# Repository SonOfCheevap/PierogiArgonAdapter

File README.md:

# Pierogi Argon Adapter
These are EAGLE files, may or may not work in KiCad

Created by the head engineer of Big PP Industries

Used to help you better interface with a Particle Argon. Newest version includes a mosfet on the SD Card Reader, and USB C.

Feature List:

-SD Card Reader

-MOSFET to reset the SD Card Reader

-USB C (Power Only)

-2 Relays

-32 Pin header for easy access to each pin

# The Family so Far:

V1(.01)

V1.1

V1.2

V1.3

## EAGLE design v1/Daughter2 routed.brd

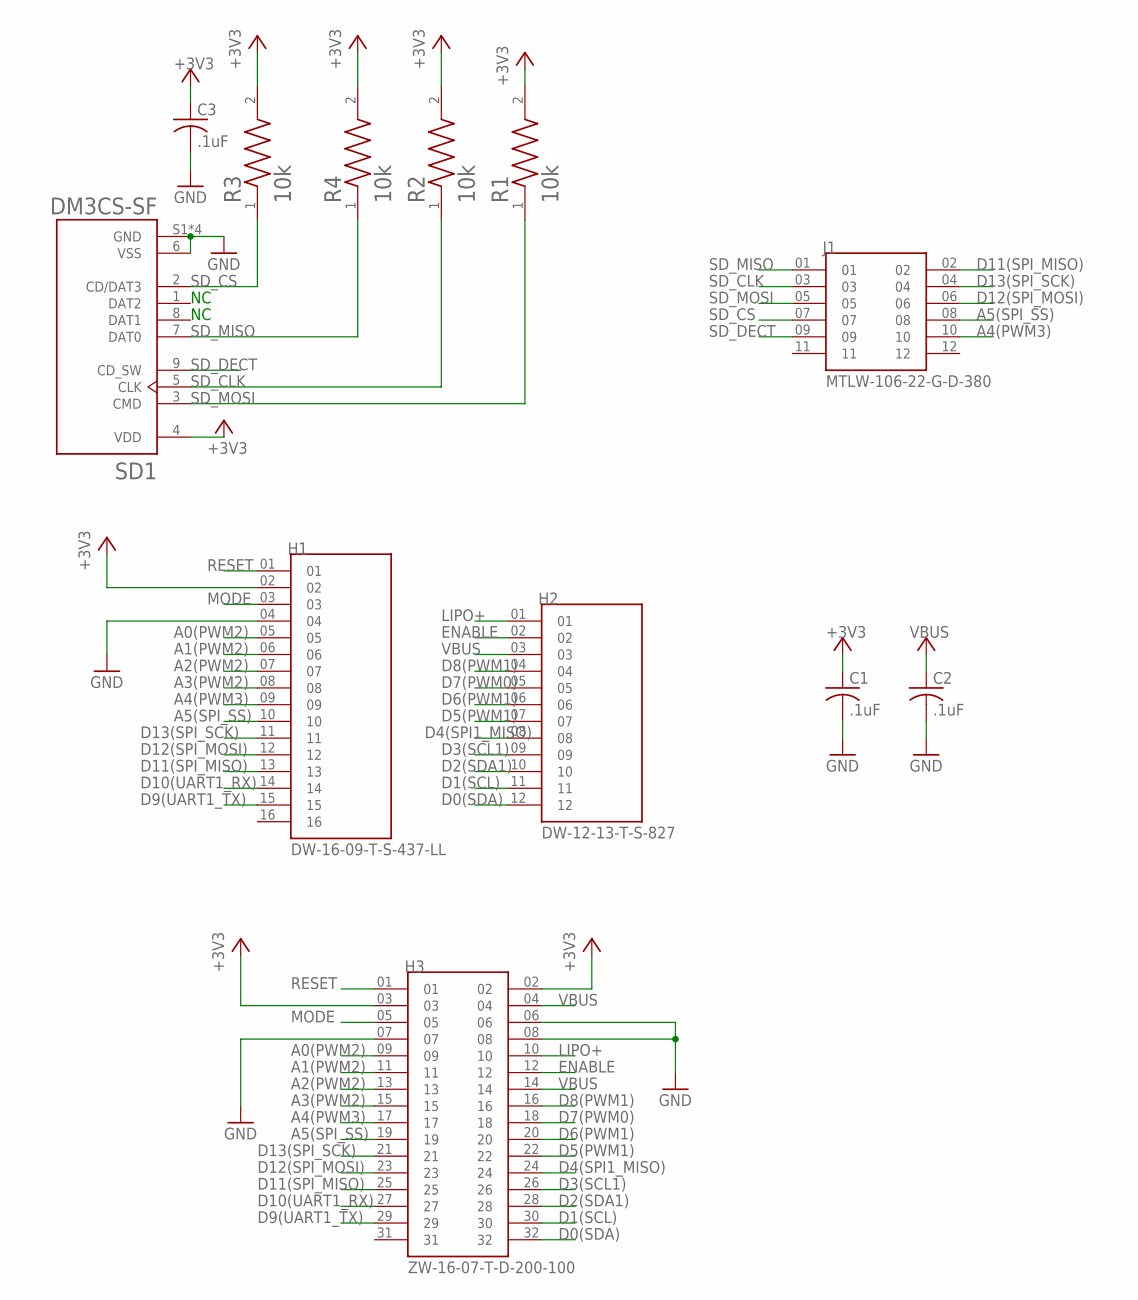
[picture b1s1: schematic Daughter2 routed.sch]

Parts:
C1, C2, C3: .1uF; C025-030X050
H1: DW-16-09-T-S-437-LL; SAMTEC_DW-16-09-T-S-437-LL
H2: DW-12-13-T-S-827; SAMTEC_DW-12-13-T-S-827
H3: ZW-16-07-T-D-200-100; SAMTEC_ZW-16-07-T-D-200-100
J1: MTLW-106-22-G-D-380; SAMTEC_MTLW-106-22-G-D-380
R1, R2, R3, R4: 10k; RESAD700W45L350D185
SD1: DM3CS-SF; HRS_DM3CS-SF

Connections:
+3V3: C1.1, C3.1, H1.02, H3.02, H3.03, R1.2, R2.2, R3.2, R4.2, SD1.4 (VDD)
A0(PWM2): H1.05, H3.09
A1(PWM2): H1.06, H3.11
A2(PWM2): H1.07, H3.13
A3(PWM2): H1.08, H3.15
A4(PWM3): H1.09, H3.17, J1.10
A5(SPI_SS): H1.10, H3.19, J1.08
D0(SDA): H2.12, H3.32
D1(SCL): H2.11, H3.30
D2(SDA1): H2.10, H3.28
D3(SCL1): H2.09, H3.26
D4(SPI1_MISO): H2.08, H3.24
D5(PWM1): H2.07, H3.22
D6(PWM1): H2.06, H3.20
D7(PWM0): H2.05, H3.18
D8(PWM1): H2.04, H3.16
D9(UART1_TX): H1.15, H3.29
D10(UART1_RX): H1.14, H3.27
D11(SPI_MISO): H1.13, H3.25, J1.02
D12(SPI_MOSI): H1.12, H3.23, J1.06
D13(SPI_SCK): H1.11, H3.21, J1.04
ENABLE: H2.02, H3.12
GND: C1.2, C2.2, C3.2, H1.04, H3.06, H3.07, H3.08, SD1.6 (VSS), SD1.S1 (GND), SD1.S2 (GND), SD1.S3 (GND), SD1.S5 (GND)
LIPO+: H2.01, H3.10
MODE: H1.03, H3.05
RESET: H1.01, H3.01
SD_CLK: J1.03, R2.1, SD1.5 (CLK)
SD_CS: J1.07, R3.1, SD1.2 (CD/DAT3)
SD_DECT: J1.09, SD1.9 (CD_SW)
SD_MISO: J1.01, R4.1, SD1.7 (DAT0)
SD_MOSI: J1.05, R1.1, SD1.3 (CMD)
VBUS: C2.1, H2.03, H3.04, H3.14

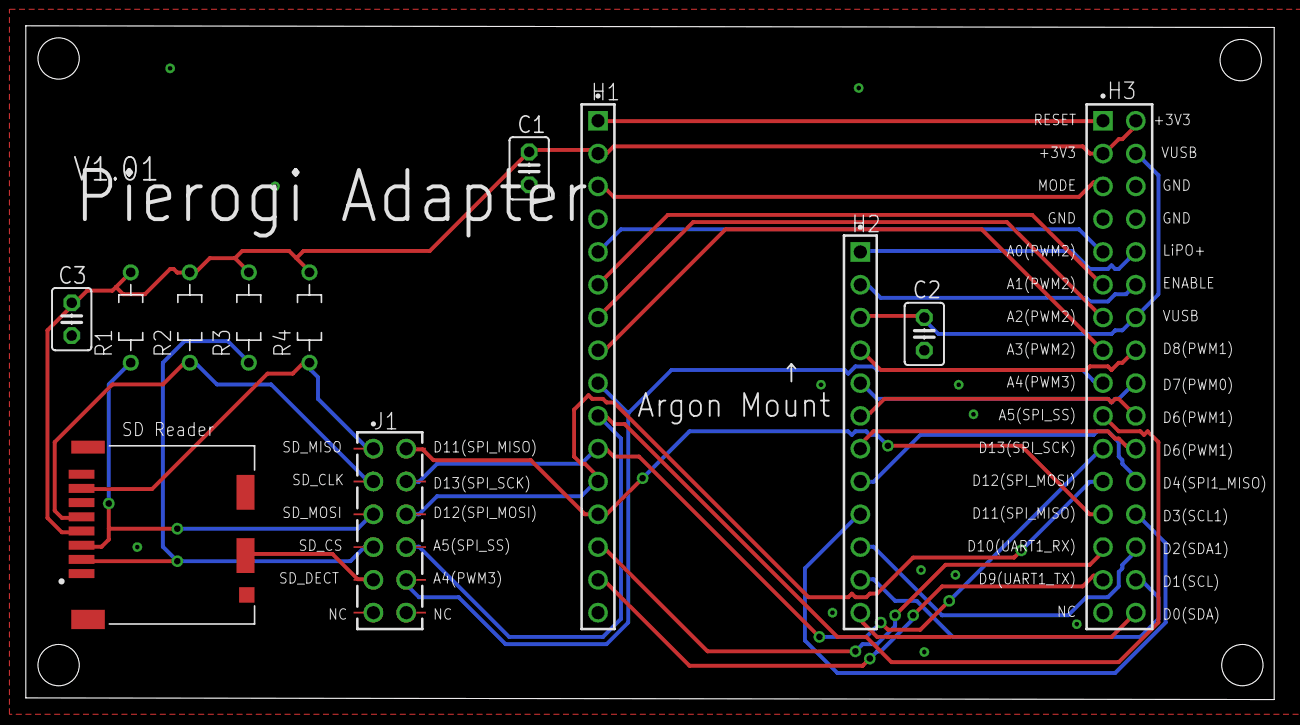
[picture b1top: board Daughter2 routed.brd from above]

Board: 2 copper layers, 96.7 x 52.2 mm, 12 parts (0 on the bottom side), 32 nets.
